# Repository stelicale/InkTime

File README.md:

# InkTime

An affordable, open-source smartwatch powered by the Nordic nRF52840 SoC and an e-paper display. Designed to be hackable, low-power, and manufacturable.

## Table of Contents

- [Block Diagram](#block-diagram)
- [Bill of Materials](#bill-of-materials)
- [Hardware Overview](#hardware-overview)
- [nRF52840 Pin Map](#nrf52840-pin-map)
- [Power Consumption](#power-consumption)
- [Test Points](#test-points)
- [Design Log](#design-log)

## Block Diagram

```
                    ╔══════════════════════════════════════════════╗
                    ║             nRF52840  (U$1)                  ║
                    ║        ARM Cortex-M4F @ 64 MHz               ║
                    ║         1 MB Flash · 256 KB RAM              ║
                    ║         BLE 5.0 · USB 2.0 FS                 ║
                    ║                                              ║
   ┌─────────────┐  ║  SPI bus: P0.02 SCK  P0.03 MOSI  P0.05 CS    ║
   │  E-Paper    │──╫──  GPIO: P0.15 DC  P0.16 RST  P0.17 BUSY     ║
   │  Display    │  ║  P1.01 EPD_PWR controls Q1 (P-MOSFET)        ║
   │  24-pin FPC │  ║                                              ║
   └─────────────┘  ║  I2C control bus: P0.06 SDA / P0.07 SCL      ║
                    ║    IC1 BQ25180 (charger config + status)     ║
   ┌─────────────┐  ║    U1  MAX17048 (fuel gauge)                 ║
   │  LiPo Cell  │──╫──    IC2 BMA423   (accelerometer)            ║
   │   1-cell    │  ║    IC3 DRV2605   (haptic driver)             ║
   └─────────────┘  ║    IC9 RT6160A   (buck-boost control)        ║
                    ║  Power path: LiPo to BQ25180 to RT6160A 3V3  ║
   ┌─────────────┐  ║                                              ║
   │  USB-C (J3) │──╫──  VBUS to BQ25180 charging path             ║
   └──────┬──────┘  ║  D+ / D- to nRF USB peripheral               ║
          │         ║                                              ║
   ┌──────┴──────┐  ║  USB ESD (D1) on D+ / D- lines               ║
   │ USBLC6-2SC6Y│  ║  GPIO lines: P0.08 IMU_INT1  P1.08 IMU_INT2  ║
   │ ESD (D1)    │  ║  P0.11 PMIC_INT  P0.12 HAPTIC_EN             ║
   └─────────────┘  ║  P0.13 SW_UP  P0.14 SW_ENT  P1.02 SW_DN      ║
   ┌─────────────┐  ║                                              ║
   │ Buttons     │──╫──  SW_UP / SW_ENT / SW_DN (EVP-AKE31A)       ║
   │ (×3 SMD)    │  ║                                              ║
   └─────────────┘  ║  32 MHz XTAL (X1) ── HFXO / RF clock         ║
                    ║  32.768 kHz XTAL (X2) ── LFXO / RTC          ║
   ┌─────────────┐  ║  ANT: L3 matching ── 2450AT18B100E           ║
   │ SWD Debug   │──╫──  SWDIO / SWDCLK / SWO / RESET              ║
   │ TC2030 (J1) │  ║      (also exposed on test pads)             ║
   └─────────────┘  ╚══════════════════════════════════════════════╝
```

## Bill of Materials

| Ref | Qty | Part Number | Description | Package | Where to buy | Datasheet |
|-----|-----|-------------|-------------|---------|--------------|-----------|
| U$1 | 1 | nRF52840-QIAA | Main SoC, BLE 5.0, Cortex-M4F | AQFN-73 7×7 mm | [JLCPCB C190794](https://jlcpcb.com/partdetail/NordicSemiconductor-nRF52840_QIAA/C190794) | [PDF](https://infocenter.nordicsemi.com/pdf/nRF52840_PS_v1.5.pdf) |
| IC1 | 1 | BQ25180YBGR | Single-cell LiPo charger, I2C, up to 1 A | 8-DSBGA 1.6×1.1 mm | [JLCPCB](https://jlcpcb.com/partdetail/TexasInstruments-BQ25180YBGR/C2678360) | [PDF](https://www.ti.com/lit/ds/symlink/bq25180.pdf) |
| IC2 | 1 | BMA423 | 3-axis accelerometer + step engine, I2C | LGA-12 2×2 mm | [JLCPCB](https://jlcpcb.com/partdetail/BoschSensortec-BMA423/C379441) | [PDF](https://www.bosch-sensortec.com/media/boschsensortec/downloads/datasheets/bst-bma423-ds000.pdf) |
| IC3 | 1 | DRV2605YZFR | Haptic actuator driver ERM/LRA, I2C | 9-BGA 1.44×1.44 mm | [JLCPCB](https://jlcpcb.com/partdetail/TexasInstruments-DRV2605YZFR/C89025) | [PDF](https://www.ti.com/lit/ds/symlink/drv2605.pdf) |
| U1 | 1 | MAX17048G+T10 | 1-cell fuel gauge, ModelGauge, I2C | TDFN-8 2×2 mm | [JLCPCB](https://jlcpcb.com/partdetail/MaximIntegrated-MAX17048GT10/C112139) | [PDF](https://datasheets.maximintegrated.com/en/ds/MAX17048-MAX17049.pdf) |
| IC9 | 1 | RT6160AWSC | I2C buck-boost DC/DC, 3.3 V output | 15-WL-CSP 1.4×2.3 mm | [JLCPCB](https://jlcpcb.com/partdetail/Richtek-RT6160AWSC/C389054) | [PDF](https://www.richtek.com/assets/product_file/RT6160A/DS6160A-00.pdf) |
| ANT1 | 1 | 2450AT18B100E | 2.45 GHz chip antenna | 3216 SMD | [JLCPCB](https://jlcpcb.com/partdetail/JohansonTechnology-2450AT18B100E/C89939) | [PDF](https://www.johansontechnology.com/datasheets/2450AT18B100E.pdf) |
| J2 | 1 | Molex 503480-2400 | 0.5 mm pitch FPC connector 24-pin | SMD RA | [JLCPCB](https://jlcpcb.com/partdetail/Molex-5034802400/C393913) | [PDF](https://www.molex.com/en-us/products/part-detail/5034802400) |
| J3 | 1 | KH-TYPE-C-16P | USB-C receptacle 16-pin | SMD | [JLCPCB C2765186](https://jlcpcb.com/partdetail/Kinghelm-KH_TYPE_C_16P/C2765186) | [PDF](https://www.kinghelm.net/product/kh-type-c-16p.html) |
| J1 | 1 | TC2030-IDC | Tag-Connect 6-pin SWD footprint | PTH (no connector) | [Tag-Connect](https://www.tag-connect.com/product/tc2030-idc) | [PDF](https://www.tag-connect.com/wp-content/uploads/bsk-pdf-manager/TC2030-IDC_1.pdf) |
| X1 | 1 | 32 MHz crystal | RF / HFXO clock | 2016 SMD | JLCPCB basic parts | Nordic ref. design |
| X2 | 1 | 32.768 kHz crystal | RTC / LFXO clock | 3215 SMD | JLCPCB basic parts | Nordic ref. design |
| L1 | 1 | Wurth 744043680 | 68 µH EPD boost inductor | 4828 SMD | [JLCPCB C408334](https://jlcpcb.com/partdetail/WurthElektronik-744043680/C408334) | [PDF](https://www.we-online.com/catalog/datasheet/744043680.pdf) |
| L2 | 1 | 10 µH inductor | nRF DCC pin choke | 0201 | JLCPCB basic parts | — |
| L3 | 1 | 15 nH inductor | RF antenna matching network | 0201 | JLCPCB basic parts | — |
| L7 | 1 | FTC252012SR47MBCA | 0.47 µH buck-boost inductor | 2016 SMD | [JLCPCB C5832368](https://jlcpcb.com/partdetail/6763488-FTC252012SR47MBCA/C5832368) | [PDF](https://product.tdk.com/en/search/inductor/inductor/smd/info?part_no=FTC252012SR47MBCA) |
| D1 | 1 | USBLC6-2SC6Y | USB ESD TVS protection | SOT-23-6 | JLCPCB basic parts | [PDF](https://www.st.com/resource/en/datasheet/usblc6-2sc6y.pdf) |
| D2, D4, D5 | 3 | MBR0530 | 30 V / 0.5 A Schottky, EPD gate circuit | SOD-123 | JLCPCB basic parts | [PDF](https://www.onsemi.com/pdf/datasheet/mbr0530t1-d.pdf) |
| Q1 | 1 | P-ch MOSFET | EPD 3.3 V power rail switch | SOT-23 | JLCPCB basic parts | — |
| Q3 | 1 | SI1308EDL-T1-GE3 | N-ch MOSFET 30 V / 1.5 A, EPD gate driver | SC-70 | JLCPCB basic parts | [PDF](https://www.vishay.com/docs/63401/si1308edl.pdf) |
| SW_UP/ENT/DN | 3 | EVP-AKE31A | SMD tactile push button | SMD | JLCPCB basic parts | [PDF](https://industrial.panasonic.com/ww/products/pt/light-touch-switches/models/EVPAKE31A) |
| R1–R18 | ~20 | Resistors | 0.47 Ω, 2.2 Ω, 3.3 kΩ, 5.1 kΩ, 7.68 kΩ, 10 kΩ | 0201 | JLCPCB basic parts | — |
| C1–C43, EPD_Cx | ~60 | Capacitors | 1 pF – 22 µF decoupling / filtering | 0201 (≤100 nF), 0402 (>100 nF) | JLCPCB basic parts | — |
| TP_* | 14 | Test pads | 3V3, VBAT, GND, SDA, SCL, SWDIO, SWDCLK, SWO, RESET… | TP20R | — | — |
| SJ1 | 1 | Solder jumper | Configuration / address selection | — | — | — |

## Hardware Overview

### nRF52840 — Main Microcontroller

The nRF52840 is the heart of InkTime. It is an ARM Cortex-M4F SoC running at 64 MHz, with 1 MB Flash, 256 KB RAM, an integrated Bluetooth 5.0 + 802.15.4 radio, hardware cryptographic accelerators, and a native USB 2.0 Full-Speed controller.

Two external crystals are mandatory:
- **X1 — 32 MHz:** feeds the high-frequency oscillator (HFXO) used by the RF transceiver.
- **X2 — 32.768 kHz:** clocks the low-frequency oscillator (LFXO) that keeps timekeeping alive during deep sleep.

The DCC pin (internal DC/DC converter) is filtered with a 10 µH inductor (L2) and bypass capacitors following Nordic's reference hardware guidelines.

### E-Paper Display — SPI interface

The display panel connects through a 24-pin, 0.5 mm pitch right-angle FPC connector (J2, Molex 503480-2400). The communication protocol is **4-wire SPI**, with three additional GPIO control lines: DC (data/command select), RST (hardware reset), and BUSY (refresh-in-progress flag).

A dedicated power rail (EPD_3V3) is produced by a boost converter using L1 (68 µH, Wurth 744043680). The rail is enabled and disabled by Q1 (P-channel MOSFET) driven from nRF pin P1.01. Gate voltages for the e-paper panel (positive and negative swing) are generated by Q3 (SI1308EDL N-MOSFET) together with diodes D2, D4, D5 (MBR0530 Schottky). Twelve 1 µF / 50 V capacitors (EPD_C1–EPD_C12, 0402) buffer the gate supply transients. Panel type is selected by a 2.2 Ω resistor on J2 pin 6.

### Battery Charger — BQ25180YBGR (IC1)

The BQ25180 is a single-cell Li-Ion/LiPo charger in an ultra-compact 8-pin DSBGA package. It is configured and monitored entirely via **I2C**. The charge current is set by R1 (10 kΩ on the TS/MR pin). The SYS output (VREG net) powers the buck-boost regulator IC9 and keeps the system alive even when the battery is absent or deeply discharged. An interrupt line (PMIC_INT → P0.11) signals the nRF whenever charging state changes. The battery connects directly to test pads TP_VBAT and TP_BAT_GND — no JST connector is used, saving vertical clearance inside the case.

Decoupling on VREG: C24 (10 µF) in parallel with C23 (100 nF). SYS output: C39 (10 µF).

### Fuel Gauge — MAX17048 (U1)

The MAX17048 estimates remaining battery capacity using the ModelGauge algorithm, which requires no current sense resistor — only a direct connection between the CELL pin and VBAT. It shares the **I2C** bus with the charger, IMU, and haptic driver, and reports state-of-charge as a percentage over I2C.

### Buck-Boost Regulator — RT6160AWSC (IC9)

The RT6160A is a 15-ball WL-CSP I2C-programmable switched-mode regulator that maintains a stable **3.3 V** output across the entire LiPo discharge range (3.0–4.2 V). The switching inductor is L7 (0.47 µH, TDK FTC252012SR47MBCA). Input bulk capacitors: C25 + C33 (22 µF each, 0402). Output capacitors: C20 + C21 (4.7 µF each, 0402). The regulator is enabled by the BQ25180's SYS output and its output voltage is fine-tuned over the shared I2C bus.

### Accelerometer / IMU — BMA423 (IC2)

The Bosch BMA423 is a 12-bit, 3-axis accelerometer in a tiny 2×2 mm LGA-12 package. It contains a built-in step counter, wrist-tilt detection, and activity classification engine — all processed on-chip without burdening the nRF. The interface is **I2C** (CSB pin pulled to VDD). Two hardware interrupt outputs (INT1 → P0.08, INT2 → P1.08) allow the watch to wake from System OFF in response to motion. The I2C address (0x18) is set by pulling SDO to GND through R3. Power decoupling: C37 (1 µF) on VDDIO and C38 (1 µF) on VDD.

### Haptic Driver — DRV2605YZFR (IC3)

The DRV2605 can drive both ERM (eccentric rotating mass) and LRA (linear resonant actuator) vibration motors using a built-in waveform library of 123 effects. Communication is over **I2C**; the EN pin (HAPTIC_EN → P0.12) is used to hard-disable the driver during sleep to eliminate quiescent current. Motor terminals are accessible at test pads TP_OP and TP_ON. VDD decoupling: C34 (100 nF, 0201).

### USB-C Port — J3 + ESD Protection (D1)

The KH-TYPE-C-16P receptacle provides VBUS for charging and exposes D+ / D− to the nRF's internal USB 2.0 Full-Speed controller. CC1 and CC2 carry 5.1 kΩ pull-down resistors (R1_USB, R2_USB) to advertise a standard 5 V / 900 mA sink. The USBLC6-2SC6Y TVS array (D1, SOT-23-6) clamps ESD transients on D+ and D−. VBUS decoupling: C42 + C43 (1500 pF each).

### SWD Debug Port — TC2030-IDC (J1)

Programming and debugging are done through a Tag-Connect TC2030-IDC footprint (no physical connector soldered, saving board space and height). It exposes SWDIO, SWDCLK, SWO, RESET, VCC, and GND. All signals are mirrored on clearly labelled test pads.

### Push Buttons

Three Panasonic EVP-AKE31A surface-mount tactile switches (SW_UP, SW_ENT, SW_DN) are debounced in hardware: each signal has a 10 kΩ pull-up to 3V3 and a 1 µF capacitor to GND forming an RC low-pass filter.

### 2.4 GHz RF Section

The Johanson 2450AT18B100E chip antenna is mounted at the board edge. The matching network between the nRF ANT pin and the antenna follows the Nordic nRF52840 reference design: a 15 nH series inductor L3, shunt capacitors C3 (1 pF), C4 (1 pF), C9 (820 pF), and C11 (100 pF). There is no copper poured and no signal routed in the area beneath the antenna — the PCB is physically cut out under the antenna footprint.

## nRF52840 Pin Map

| Pin | Signal | Destination | Bus / Function | Reason for choice |
|-----|--------|-------------|----------------|-------------------|
| P0.00 / XL1 | XL1 | X2 pin 2 | LFXO — 32.768 kHz crystal | Dedicated crystal pins, cannot be reassigned |
| P0.01 / XL2 | XL2 | X2 pin 1 | LFXO — 32.768 kHz crystal | Dedicated crystal pins, cannot be reassigned |
| P0.02 | SCK | J2 pin 13 → EPD | SPI clock | Flexible GPIO; SPIM peripheral is fully remappable |
| P0.03 | MOSI | J2 pin 14 → EPD | SPI data out | Flexible GPIO; chosen to keep SPI traces grouped |
| P0.05 | EPD_CS | J2 pin 12 → EPD | SPI chip select | Flexible GPIO; adjacent to SCK/MOSI on port 0 |
| P0.06 | SDA | IC1, IC2, IC3, U1 | I2C data | Close to BQ25180 and BMA423 on PCB → short trace |
| P0.07 | SCL | IC1, IC2, IC3, U1 | I2C clock | Paired with P0.06 for I2C bus |
| P0.08 | IMU_INT1 | BMA423 INT1 | GPIO input (wake) | Free pin; interrupt-capable on port 0 |
| P0.11 | PMIC_INT | BQ25180 !INT | GPIO input | Free pin; interrupt-capable |
| P0.12 | HAPTIC_EN | DRV2605 EN | GPIO output | Free pin; any output-capable GPIO works |
| P0.13 | SW_UP | SW_UP tactile | GPIO input, pull-up | Free pin after peripheral assignment |
| P0.14 | SW_ENT | SW_ENT tactile | GPIO input, pull-up | Free pin after peripheral assignment |
| P0.15 | EPD_DC | J2 pin 11 | GPIO output | Grouped with other EPD pins on port 0 |
| P0.16 | EPD_RST | J2 pin 10 | GPIO output | Grouped with other EPD pins on port 0 |
| P0.17 | EPD_BUSY | J2 pin 9 | GPIO input | Grouped with other EPD pins on port 0 |
| P0.18 / RESET | RESET | J1, TP_RESET | Hardware reset | Dedicated reset pin |
| P1.00 | SWO | J1, TP_SWO | SWD trace output | Port 1 free pin; trace output on any GPIO |
| P1.01 | EPD_PWR | Q1 gate | GPIO output — EPD rail enable | Free port 1 pin; any output GPIO works |
| P1.02 | SW_DN | SW_DN tactile | GPIO input, pull-up | Free pin after peripheral assignment |
| P1.08 | IMU_INT2 | BMA423 INT2 | GPIO input (wake) | Free pin; interrupt-capable on port 1 |
| SWDCLK | SWDCLK | J1, TP_SWDCLK | SWD debug clock | Dedicated SWD pin |
| SWDIO | SWDIO | J1, TP_SWDIO | SWD debug data | Dedicated SWD pin |
| DCC | — | L2 (10 µH) | Internal DC/DC choke | Required by nRF power management |
| XC1/XC2 | — | X1 (32 MHz) | HFXO — RF clock | Dedicated crystal input pins |
| ANT | — | L3 → ANT1 | 2.4 GHz RF output | Dedicated antenna pad |
| VDD / VDDH | 3V3 | RT6160AWSC output | 3.3 V supply | — |
| DEC1–DEC6 | — | 100 nF / 12 pF caps | Internal regulator decoupling | Per Nordic HW guidelines |

## Power Consumption

Estimated figures derived from component datasheets and Nordic power profiler reference data:

| Operating Mode | nRF52840 | E-Paper | BMA423 | DRV2605 | System Total |
|----------------|----------|---------|--------|---------|--------------|
| BLE advertising (1 s interval) | ~15 mA avg | 0 mA | 0.13 mA | 0 mA | **~15 mA** |
| Display refresh | ~3 mA | ~30 mA peak | 0.13 mA | 0 mA | **~33 mA** |
| Haptic event | ~5 mA | 0 mA | 0 mA | ~60 mA | **~65 mA** |
| System OFF (deep sleep) | 2.5 µA | 0 mA | 0 µA | 0 µA | **~3 µA** |

Assuming a 180 mAh LiPo cell, BLE advertising every 1 second, and a display refresh once per minute, the estimated battery life is roughly **5–7 days**.

## Test Points

All test pads are silkscreened with their signal name (signal name only — no component value on silkscreen):

| Pad name | Signal |
|----------|--------|
| TP_3V3 | 3.3 V regulated output (RT6160AWSC) |
| TP_VBAT | Raw battery positive terminal |
| TP_BAT_GND | Battery negative terminal |
| TP_GND | System ground |
| TP_VREG | BQ25180 SYS / VREG output |
| TP_SDA | I2C data line |
| TP_SCL | I2C clock line |
| TP_SWDIO | SWD data |
| TP_SWDCLK | SWD clock |
| TP_SWO | SWD trace / serial wire output |
| TP_RESET | System reset |
| TP_OP / TP_ON | Haptic motor + / − terminals |

## Design Log

A summary of key decisions and accepted rule deviations:

- **PCB thickness: 1 mm.** The standard 1.6 mm board would not fit inside the provided enclosure. All mechanical clearances were verified against the case STEP file.
- **Components on TOP layer only.** Required by the project specification. No components are placed on the BOTTOM layer.
- **Ground planes on both layers.** The TOP and BOTTOM copper pours are both tied to GND. Via stitching is applied across the whole board, with extra density near the RF circuitry.
- **Antenna keepout.** The area under ANT1 (2450AT18B100E) has no copper pour, no signal routing, and a PCB cutout — all three constraints required by the Nordic reference design.
- **Power trace widths.** All power nets (3V3, VBAT, VBUS, VREG) are routed at 0.3 mm. Signal traces use a minimum of 0.15 mm. Traces that pass under BGA pads are narrowed to fit within the available fanout geometry.
- **No right-angle bends.** All trace corners use 45° chamfers throughout the board.
- **Battery direct-soldered.** The LiPo battery is connected directly to TP_VBAT and TP_BAT_GND rather than using the JST connector it ships with. This eliminates ~1 mm of vertical height that would otherwise violate the case Z-clearance.
- **Accepted ERC warning:** "Only INPUT pins on NET ID" is a known false positive in this tool version and is explicitly allowed by the project guidelines.
- **Accepted dimension errors:** The board outline DRC reports errors at the three button cutouts and the USB-C aperture. These are structural slots required by the enclosure and are permitted per project guidelines.
- **Decoupling capacitor placement.** Every 100 nF decoupling capacitor is placed within one pad-length of the IC power pin it serves, on the same layer.

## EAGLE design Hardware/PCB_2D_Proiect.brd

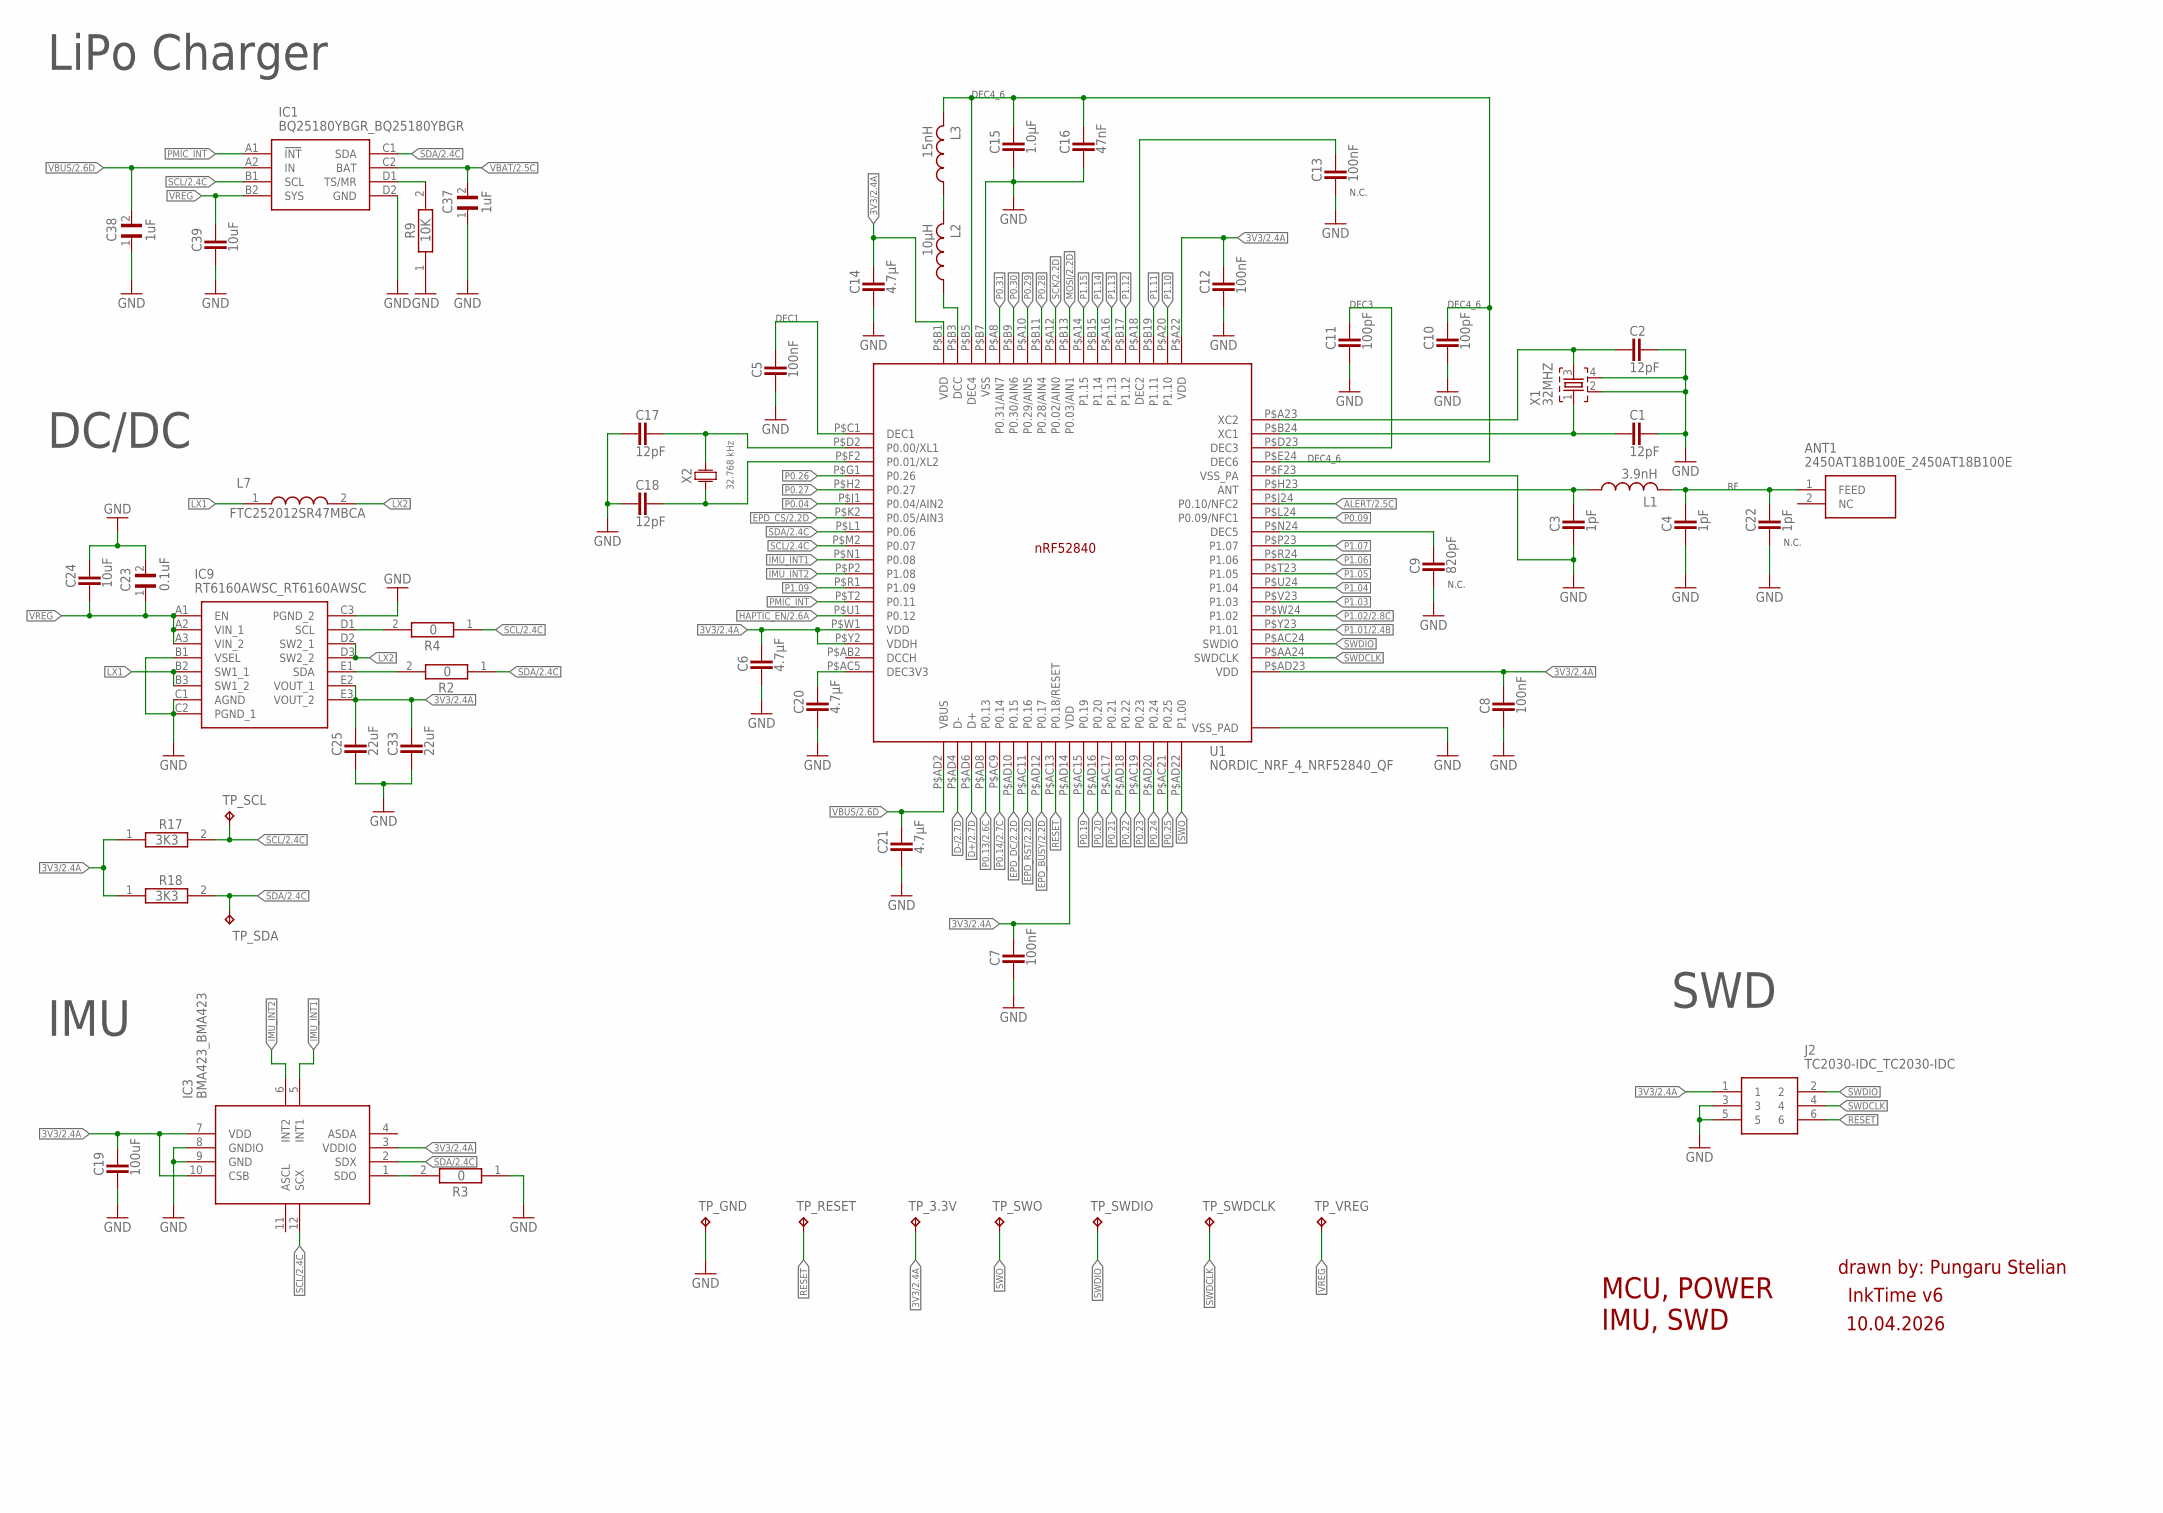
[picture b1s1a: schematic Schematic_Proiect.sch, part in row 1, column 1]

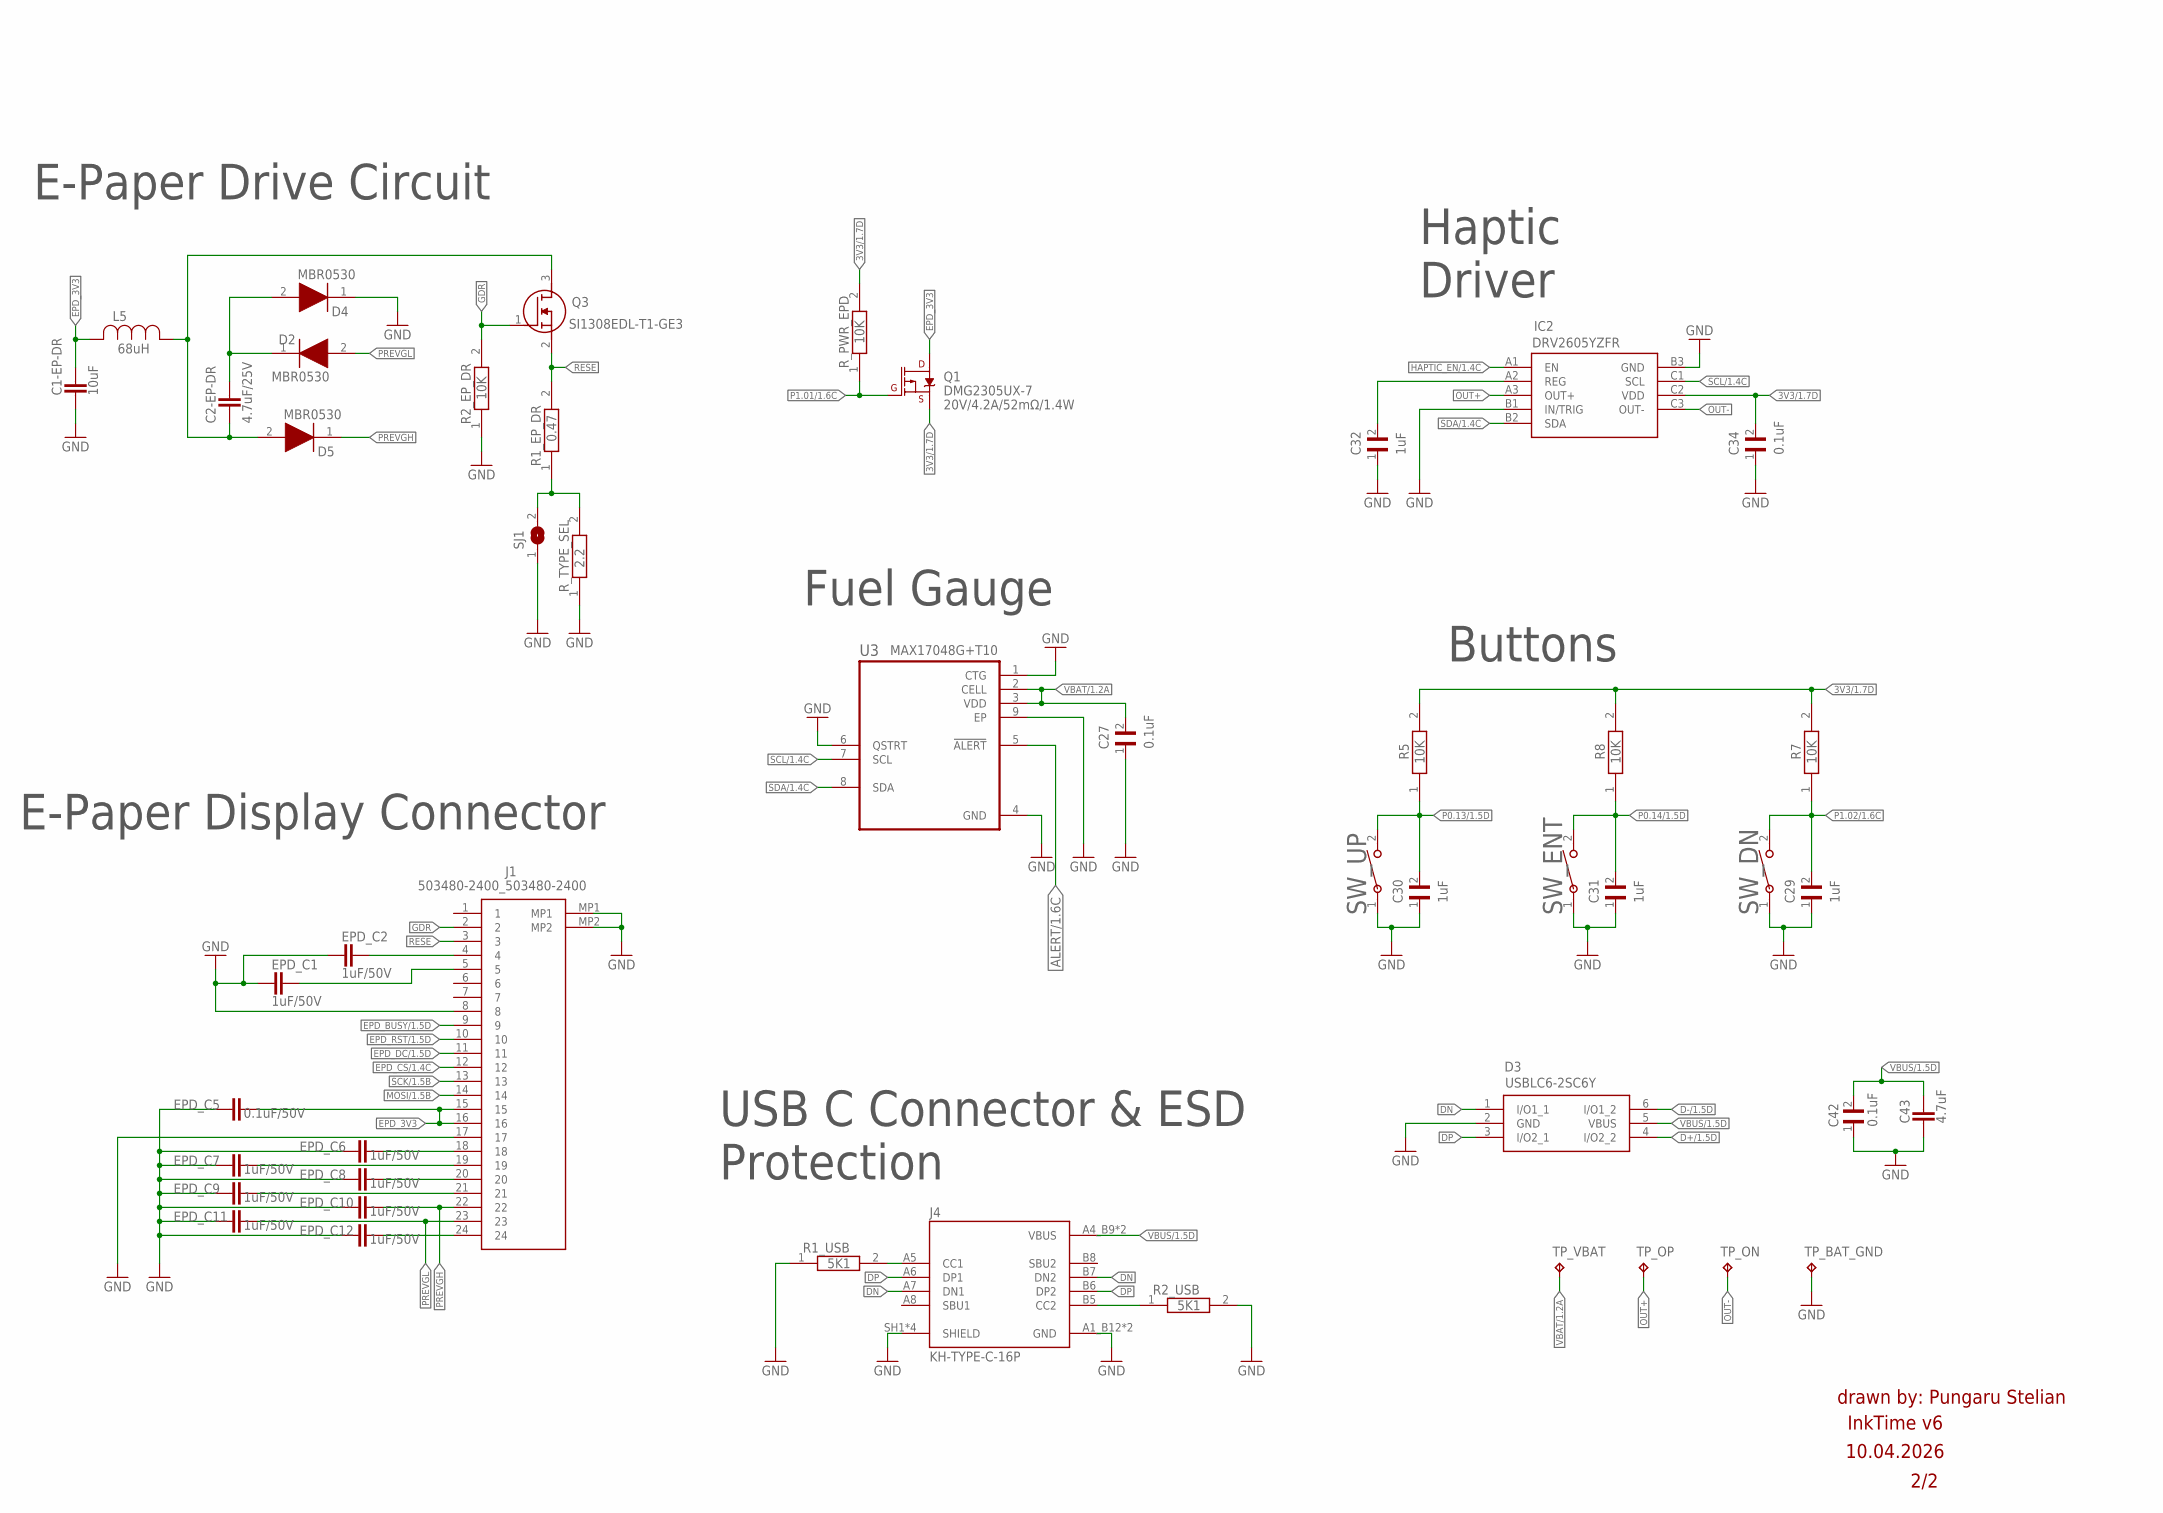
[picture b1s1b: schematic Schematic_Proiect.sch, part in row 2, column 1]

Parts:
ANT1: 2450AT18B100E_2450AT18B100E; 2450AT18B100E_ANTC3216X140N
C1, C2, C17, C18: 12pF; CAPC1005X60
C1-EP-DR, C24, C39: 10uF; CAPC1005X60
C2-EP-DR: 4.7uF/25V; CAPC1005X60
C3, C4, C22: 1pF; CAPC1005X60
C5, C7, C8, C12, C13: 100nF; CAPC1005X60
C6, C14, C20, C21: 4.7µF; CAPC1005X60
C9: 820pF; CAPC1005X60
C10, C11: 100pF; CAPC1005X60
C15: 1.0µF; CAPC1005X60
C16: 47nF; CAPC1005X60
C19: 100uF; CAPC1005X60
C23, C27, C29, C30, C31, C32, C34, C37, C38, C42: GRM011R60J152KE01L_2_GRM011R60J152KE01L; GRM011R60J152KE01L_2_CAPC0201X13N
C25, C33: 22uF; CAPC1005X60
C43: 4.7uF; CAPC1005X60
D2, D4, D5: ESP32_C6_LIBRARY_5_MBR0530; ESP32_C6_LIBRARY_5_SOD3716X135N
D3: ESP32_C6_LIBRARY_3_USBLC6-2SC6Y; ESP32_C6_LIBRARY_3_SOT95P280X145-6N
EPD_C1, EPD_C2, EPD_C6, EPD_C7, EPD_C8, EPD_C9, EPD_C10, EPD_C11, EPD_C12: 1uF/50V; CAPC1005X60
EPD_C5: 0.1uF/50V; CAPC1005X60
IC1: BQ25180YBGR_BQ25180YBGR; BQ25180YBGR_BGA8C40P2X4_100X155X50
IC2: DRV2605YZFR_DRV2605YZFR; DRV2605YZFR_BGA9C50P3X3_144X144X62
IC3: BMA423_BMA423
IC9: RT6160AWSC_RT6160AWSC; RT6160AWSC_BGA15C40P3X5_140X230X60
J1: 503480-2400_503480-2400; 503480-2400_5034802400
J2: TC2030-IDC_TC2030-IDC; TC2030-IDC_TC2030IDC
J4: KH-TYPE-C-16P_KH-TYPE-C-16P; KH-TYPE-C-16P_KINGHELM_KH-TYPE-C-16P
L1: 3.9nH; NORDIC_NRF_2_RESC0402_L
L2: 10µH; NORDIC_NRF_2_RESC0402_L
L3: 15nH; NORDIC_NRF_2_RESC0402_L
L5: ESP32_C6_LIBRARY_2_744043680IND_4828-WE-TPC_WRE; ESP32_C6_LIBRARY_2_IND_4828-WE-TPC_WRE
L7: MLP2016SR47MT0S1_FTC252012SR47MBCA; MLP2016SR47MT0S1_INDC2016X100N
Q1: 20V/4.2A/52mΩ/1.4W; ESP32_C6_LIBRARY_4_ESP32_C6_LIBRARY_4_ESP32_C6_LIBRARY_4_ES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
Q3: ESP32_C6_LIBRARY_6_SI1308EDL-T1-GE3; ESP32_C6_LIBRARY_6_SOT65P210X110-3N
R1_EP_DR, R1_USB, R2, R2_EP_DR, R2_USB, R3, R4, R5, R7, R8, R9, R17, R18: CPF0201D7K68C1_CPF0201D7K68C1; CPF0201D7K68C1_0201
R_PWR_EPD: CPF0201D7K68C1_CPF0201D7K68C1; CPF0201D7K68C1_0201
R_TYPE_SEL: CPF0201D7K68C1_CPF0201D7K68C1; CPF0201D7K68C1_0201
SJ1: ESP32_C6_LIBRARY_7_JUMPER_SJ
SW_DN: 2025-10-22_07-23-44_LIBRARY_EVP-AKE31ASW_EVP-AKE3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; 2025-10-22_07-23-44_LIBRARY_SW_EVP-AKE31A_PAN
SW_ENT: 2025-10-22_07-23-44_LIBRARY_EVP-AKE31ASW_EVP-AKE3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; 2025-10-22_07-23-44_LIBRARY_SW_EVP-AKE31A_PAN
SW_UP: 2025-10-22_07-23-44_LIBRARY_EVP-AKE31ASW_EVP-AKE3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; 2025-10-22_07-23-44_LIBRARY_SW_EVP-AKE31A_PAN
TP_3.3V: HECTOR_WATCH_1_TPTP20R; HECTOR_WATCH_1_TP20R
TP_BAT_GND: HECTOR_WATCH_1_TPTP20R; HECTOR_WATCH_1_TP20R
TP_GND: HECTOR_WATCH_1_TPTP20R; HECTOR_WATCH_1_TP20R
TP_ON: HECTOR_WATCH_1_TPTP20R; HECTOR_WATCH_1_TP20R
TP_OP: HECTOR_WATCH_1_TPTP20R; HECTOR_WATCH_1_TP20R
TP_RESET: HECTOR_WATCH_1_TPTP20R; HECTOR_WATCH_1_TP20R
TP_SCL: HECTOR_WATCH_1_TPTP20R; HECTOR_WATCH_1_TP20R
TP_SDA: HECTOR_WATCH_1_TPTP20R; HECTOR_WATCH_1_TP20R
TP_SWDCLK: HECTOR_WATCH_1_TPTP20R; HECTOR_WATCH_1_TP20R
TP_SWDIO: HECTOR_WATCH_1_TPTP20R; HECTOR_WATCH_1_TP20R
TP_SWO: HECTOR_WATCH_1_TPTP20R; HECTOR_WATCH_1_TP20R
TP_VBAT: HECTOR_WATCH_1_TPTP20R; HECTOR_WATCH_1_TP20R
TP_VREG: HECTOR_WATCH_1_TPTP20R; HECTOR_WATCH_1_TP20R
U1: NORDIC_NRF_4_NRF52840_QF; NORDIC_NRF_4_AQFN50P700X700X85_HS-74N
U3: ESP32_C6_LIBRARY_MAX17048G+T10; ESP32_C6_LIBRARY_SON50P200X200X80-9N
X1: 32MHZ; NORDIC_NRF_BT-XTAL_2016_N
X2: FC-135; XTAL330X1051X90N

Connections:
3V3/1.7D: Q1.2 (S)
3V3/2.4A: TP_3.3V.TP
ALERT/1.6C: U3.5 (!ALERT)
ALERT/2.5C: U1.P$J24 (P0.10/NFC2)
D+/1.5D: D3.4 (I/O2_2)
D+/2.7D: U1.P$AD6 (D+)
D-/1.5D: D3.6 (I/O1_2)
D-/2.7D: U1.P$AD4 (D-)
DN: D3.1 (I/O1_1)
DP: D3.3 (I/O2_1)
EPD_3V3: C1-EP-DR.1, L5.2
EPD_BUSY/1.5D: J1.9
EPD_BUSY/2.2D: U1.P$AD12 (P0.17)
EPD_CS/1.4C: J1.12
EPD_CS/2.2D: U1.P$K2 (P0.05/AIN3)
EPD_DC/1.5D: J1.11
EPD_DC/2.2D: U1.P$AD10 (P0.15)
EPD_RST/1.5D: J1.10
EPD_RST/2.2D: U1.P$AC11 (P0.16)
GDR: Q3.1 (G), R2_EP_DR.2
GND: C1.1, C1-EP-DR.2, C2.1, C3.2, C4.2, C5.2, C6.2, C7.2, C8.2, C9.2, C10.2, C11.2, C12.2, C13.2, C14.2, C15.2, C16.2, C17.2, C18.2, C19.2, C20.2, C21.2, C22.2, C23.2, C24.1, C25.2, C27.1, C29.1, C30.1, C31.1, C32.1, C33.2, C34.1, C37.1, C38.1, C39.2, C42.1, C43.2, D3.2 (GND), D4.1 (K), EPD_C1.2, EPD_C2.2, EPD_C5.2, EPD_C6.2, EPD_C7.2, EPD_C8.2, EPD_C9.2, EPD_C10.2, EPD_C11.2, EPD_C12.2, IC1.D2 (GND), IC2.B1 (IN/TRIG), IC2.B3 (GND), IC3.8 (GNDIO), IC3.9 (GND), IC9.B1 (VSEL), IC9.C1 (AGND), IC9.C2 (PGND_1), IC9.C3 (PGND_2), J1.8, J1.17, J1.MP1, J1.MP2, J2.3, J2.5, J4.A1_B12 (GND), J4.A12_B1 (GND), J4.SH1 (SHIELD), J4.SH2 (SHIELD), J4.SH3 (SHIELD), J4.SH4 (SHIELD), R1_USB.1, R2_EP_DR.1, R2_USB.2, R3.1, R9.1, R_TYPE_SEL.1, SJ1.1, SW_DN.1, SW_ENT.1, SW_UP.1, TP_BAT_GND.TP, TP_GND.TP, U1.P$74 (VSS_PAD), U1.P$75 (VSS_PAD), U1.P$76 (VSS_PAD), U1.P$77 (VSS_PAD), U1.P$78 (VSS_PAD), U1.P$79 (VSS_PAD), U1.P$80 (VSS_PAD), U1.P$81 (VSS_PAD), U1.P$82 (VSS_PAD), U1.P$83 (VSS_PAD), U1.P$84 (VSS_PAD), U1.P$85 (VSS_PAD), U1.P$86 (VSS_PAD), U1.P$87 (VSS_PAD), U1.P$88 (VSS_PAD), U1.P$89 (VSS_PAD), U1.P$90 (VSS_PAD), U1.P$B7 (VSS), U1.P$F23 (VSS_PA), U3.1 (CTG), U3.4 (GND), U3.6 (QSTRT), U3.9 (EP), X1.2, X1.4
HAPTIC_EN/1.4C: IC2.A1 (EN)
HAPTIC_EN/2.6A: U1.P$U1 (P0.12)
IMU_INT1: IC3.5 (INT1)
IMU_INT2: IC3.6 (INT2)
LX1: L7.1
LX2: L7.2
MOSI/1.5B: J1.14
MOSI/2.2D: U1.P$B13 (P0.03/AIN1)
unnamed: IC9.D1 (SCL), R4.2
unnamed: IC1.D1 (TS/MR), R9.2
unnamed: IC9.D2 (SW2_1), IC9.D3 (SW2_2)
unnamed: IC9.E1 (SDA), R2.2
unnamed: C25.1, C33.1, IC9.E2 (VOUT_1), IC9.E3 (VOUT_2)
unnamed: R17.1, R18.1
unnamed: IC9.B2 (SW1_1), IC9.B3 (SW1_2)
unnamed: C23.1, C24.2, IC9.A1 (EN), IC9.A2 (VIN_1), IC9.A3 (VIN_2)
unnamed: R17.2, TP_SCL.TP
unnamed: R18.2, TP_SDA.TP
unnamed: IC3.1 (SDO), R3.2
unnamed: C19.1, IC3.7 (VDD), IC3.10 (CSB)
unnamed: C8.1, U1.P$AD23 (VDD)
unnamed: C9.1, U1.P$N24 (DEC5)
unnamed: C2.2, U1.P$A23 (XC2), X1.3
unnamed: C3.1, L1.1, U1.P$H23 (ANT)
unnamed: ANT1.1 (FEED), C4.1, C22.1, L1.2
unnamed: C2-EP-DR.2, D5.2 (A), L5.1, Q3.3 (D)
unnamed: C1.2, U1.P$B24 (XC1), X1.1
unnamed: C11.1, U1.P$D23 (DEC3)
unnamed: C20.1, U1.P$AC5 (DEC3V3)
unnamed: C6.1, U1.P$W1 (VDD), U1.P$Y2 (VDDH)
unnamed: C14.1, U1.P$B1 (VDD)
unnamed: C12.1, U1.P$A22 (VDD)
unnamed: C7.1, U1.P$AD14 (VDD)
unnamed: L2.2, L3.1
unnamed: C10.1, C15.1, C16.1, L3.2, U1.P$B5 (DEC4), U1.P$E24 (DEC6)
unnamed: C13.1, U1.P$A18 (DEC2)
unnamed: C2-EP-DR.1, D2.1 (K), D4.2 (A)
unnamed: C18.1, U1.P$F2 (P0.01/XL2), X2.1
unnamed: C21.1, U1.P$AD2 (VBUS)
unnamed: C17.1, U1.P$D2 (P0.00/XL1), X2.2
unnamed: C5.1, U1.P$C1 (DEC1)
unnamed: R1_EP_DR.1, R_TYPE_SEL.2, SJ1.2
unnamed: EPD_C2.1, J1.4
unnamed: EPD_C1.1, J1.5
unnamed: J4.A4_B9 (VBUS), J4.A9_B4 (VBUS)
unnamed: C27.2, U3.2 (CELL), U3.3 (VDD)
unnamed: L2.1, U1.P$B3 (DCC)
unnamed: J4.B5 (CC2), R2_USB.1
unnamed: J4.A5 (CC1), R1_USB.2
unnamed: EPD_C5.1, J1.15, J1.16
unnamed: EPD_C6.1, J1.18
unnamed: EPD_C7.1, J1.19
unnamed: EPD_C8.1, J1.20
unnamed: EPD_C9.1, J1.21
unnamed: EPD_C10.1, J1.22
unnamed: EPD_C11.1, J1.23
unnamed: EPD_C12.1, J1.24
unnamed: C34.2, IC2.C2 (VDD)
unnamed: C32.2, IC2.A2 (REG)
unnamed: R5.2, R7.2, R8.2
OUT+: TP_OP.TP
OUT-: TP_ON.TP
P0.04: U1.P$J1 (P0.04/AIN2)
P0.09: U1.P$L24 (P0.09/NFC1)
P0.13/1.5D: C30.2, R5.1, SW_UP.2
P0.13/2.6C: U1.P$AD8 (P0.13)
P0.14/1.5D: C31.2, R8.1, SW_ENT.2
P0.14/2.7C: U1.P$AC9 (P0.14)
P0.19: U1.P$AC15 (P0.19)
P0.20: U1.P$AD16 (P0.20)
P0.21: U1.P$AC17 (P0.21)
P0.22: U1.P$AD18 (P0.22)
P0.23: U1.P$AC19 (P0.23)
P0.24: U1.P$AD20 (P0.24)
P0.25: U1.P$AC21 (P0.25)
P0.26: U1.P$G1 (P0.26)
P0.27: U1.P$H2 (P0.27)
P0.28: U1.P$B11 (P0.28/AIN4)
P0.29: U1.P$A10 (P0.29/AIN5)
P0.30: U1.P$B9 (P0.30/AIN6)
P0.31: U1.P$A8 (P0.31/AIN7)
P1.01/1.6C: Q1.1 (G), R_PWR_EPD.1
P1.01/2.4B: U1.P$Y23 (P1.01)
P1.02/1.6C: C29.2, R7.1, SW_DN.2
P1.02/2.8C: U1.P$W24 (P1.02)
P1.03: U1.P$V23 (P1.03)
P1.04: U1.P$U24 (P1.04)
P1.05: U1.P$T23 (P1.05)
P1.06: U1.P$R24 (P1.06)
P1.07: U1.P$P23 (P1.07)
P1.09: U1.P$R1 (P1.09)
P1.10: U1.P$A20 (P1.10)
P1.11: U1.P$B19 (P1.11)
P1.12: U1.P$B17 (P1.12)
P1.13: U1.P$A16 (P1.13)
P1.14: U1.P$B15 (P1.14)
P1.15: U1.P$A14 (P1.15)
PMIC_INT: IC1.A1 (!INT)
PREVGH: D5.1 (K)
PREVGL: D2.2 (A)
RESE: Q3.2 (S), R1_EP_DR.2
RESET: TP_RESET.TP
SCK/1.5B: J1.13
SCK/2.2D: U1.P$A12 (P0.02/AIN0)
SCL/1.4C: IC2.C1 (SCL), U3.7 (SCL)
SCL/2.4C: IC1.B1 (SCL)
SDA/1.4C: IC2.B2 (SDA), U3.8 (SDA)
SDA/2.4C: IC1.C1 (SDA)
SWDCLK: TP_SWDCLK.TP, U1.P$AA24 (SWDCLK)
SWDIO: TP_SWDIO.TP
SWO: TP_SWO.TP, TP_VREG.TP
VBAT/1.2A: TP_VBAT.TP
VBAT/2.5C: C37.2, IC1.C2 (BAT)
VBUS/1.5D: C42.2, C43.1
VBUS/2.6D: C38.2, IC1.A2 (IN)
VREG: C39.1, IC1.B2 (SYS)

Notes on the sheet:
LiPo Charger
DC/DC
IMU
SWD
N.C.
DEC4_6
DEC3
DEC1
E-Paper Drive Circuit
E-Paper Display Connector
Fuel Gauge
USB C Connector & ESD Protection
Buttons
Haptic Driver
MCU, POWER IMU, SWD
drawn by: Pungaru Stelian
InkTime v6
10.04.2026
2/2

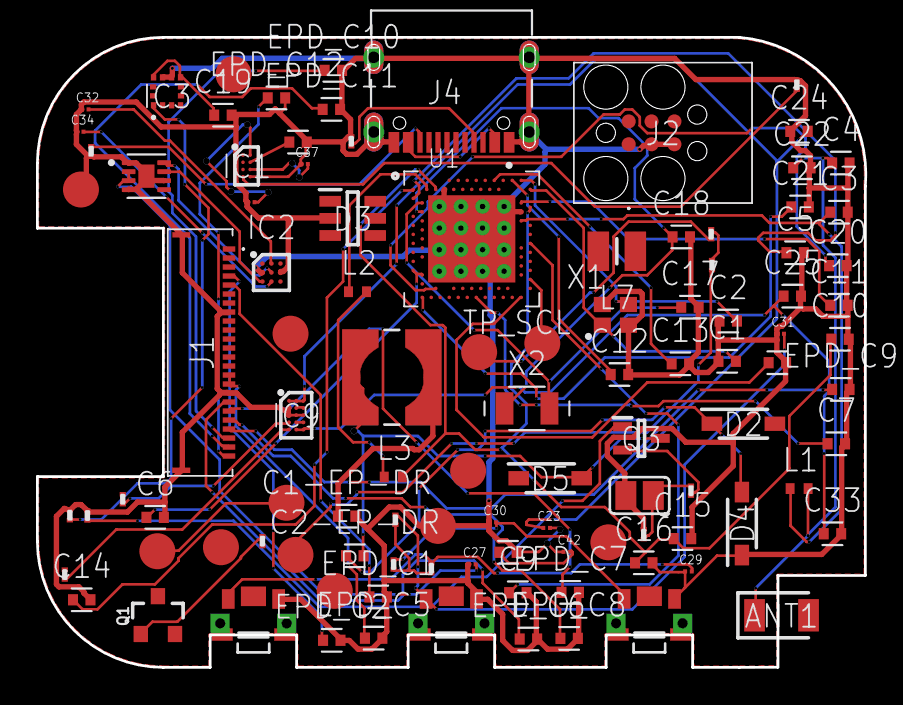
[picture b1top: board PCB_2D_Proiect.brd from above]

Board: 2 copper layers, 46.0 x 35.0 mm, 104 parts (0 on the bottom side), 68 nets.

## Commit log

2026-04-10 schematic and board
2026-04-12 added
2026-04-15 fix antenna
2026-04-16 named the frame
2026-04-17 added ground pours and via stitching
2026-04-18 fixed silkscreen component names
2026-04-20 partial fix #5

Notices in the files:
parts and their libraries:
COPYRIGHT: Copyright (C) 2024 Ultra Librarian. All rights reserved.
COPYRIGHT: Copyright (C) 2025 Ultra Librarian. All rights reserved.
